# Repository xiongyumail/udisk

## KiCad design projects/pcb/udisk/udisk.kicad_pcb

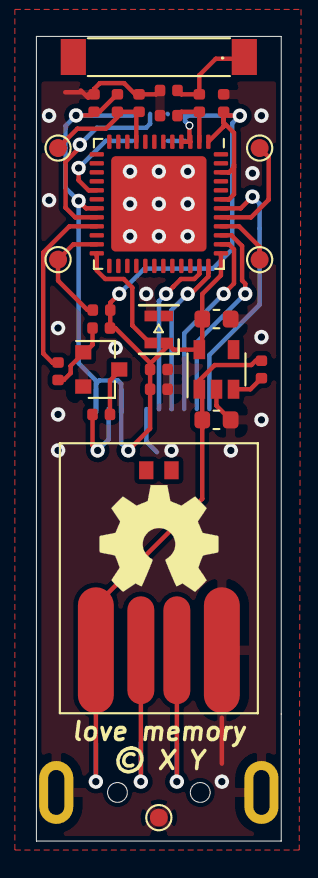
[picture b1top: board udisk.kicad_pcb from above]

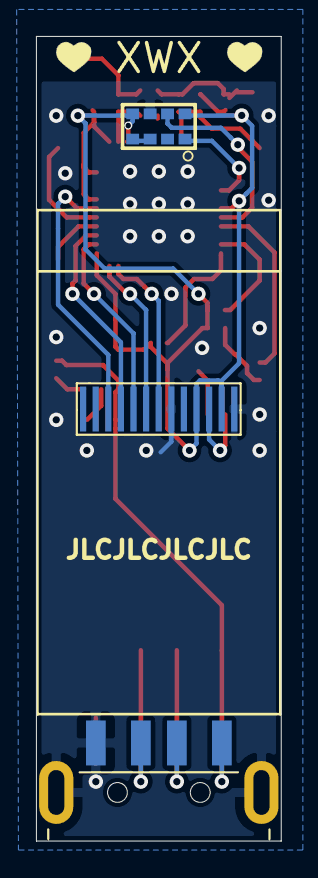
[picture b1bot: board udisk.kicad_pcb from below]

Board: 2 copper layers, 13.6 x 44.7 mm, 30 parts (3 on the bottom side), 25 nets.

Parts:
AE1: ANT; AN9520
C1, C2: 1uF; C_0603_1608Metric
C3, C4, C5, C8, C11: 0.1uF; C_0402_1005Metric
C6, C7: NC; C_0402_1005Metric
D1: WS2812B-0807
J1: USB_A; USB_A_2.0_Male
L1: NC; L_0402_1005Metric
LCD1: IPS0.9'160x80
Q1: S8050; SOT-23
R1: 100K; R_0402_1005Metric
R2: 1K; R_0402_1005Metric
R3, R5, R6: 10K; R_0402_1005Metric
R4: 10; R_0402_1005Metric
TP1: TXD; TestPoint_Pad_D1.0mm
TP2: RXD; TestPoint_Pad_D1.0mm
TP3: EN; TestPoint_Pad_D1.0mm
TP4: GPIO0; TestPoint_Pad_D1.0mm
TP5: GND; TestPoint_Pad_D1.0mm
U1: RT9013; SOT-23-5
U2: APDS-9960
U3: ESP32-PICO-D4; QFN-48-1EP_7x7mm_P0.5mm_EP5.3x5.3mm
U5: udisk

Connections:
+3V3: C2.1, C3.2, C4.1, C8.1, C11.1, D1.1, LCD1.10, LCD1.12, R3.1, R5.1, R6.1, U1.5, U2.5, U2.8, U3.1, U3.3, U3.4, U3.19, U3.37, U3.43, U3.46
/D+: J1.3, U5.3
/D-: J1.2, U5.2
/DIN: D1.4, U3.24
/ESP32-PICO-D4/EN: C5.1, R5.2, TP3.1, U3.9
/ESP32-PICO-D4/GPIO0: R6.2, TP4.1, U3.23
/ESP32-PICO-D4/RXD: TP2.1, U3.40
/ESP32-PICO-D4/TXD: TP1.1, U3.41
/LCD160x80/LEDK: LCD1.11, R4.1
/LCD_BLK: R2.2, U3.21
/LCD_CLK: LCD1.4, U3.39
/LCD_CS1: LCD1.7, U3.35
/LCD_DC: LCD1.5, U3.38
/LCD_MOSI: LCD1.3, U3.42
/LCD_RES: LCD1.6, U3.36
/SCL: U2.7, U3.20
/SDA: U2.1, U3.17
GND: C1.2, C2.2, C3.1, C4.2, C5.2, C6.2, C7.2, C8.2, C11.2, D1.3, J1.4, J1.5, LCD1.8, LCD1.13, Q1.2, TP5.1, U1.2, U2.6, U3.49, U5.4
unnamed: AE1.1, C6.1, L1.2
unnamed: C7.1, L1.1, U3.2
unnamed: Q1.1, R2.1, R3.2
unnamed: Q1.3, R4.2
unnamed: R1.1, U1.3
unnamed: U2.3, U2.4
VBUS: C1.1, J1.1, R1.2, U1.1, U5.1

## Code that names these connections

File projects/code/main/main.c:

#include <stdio.h>
#include <stdlib.h>
#include <stdio.h>
#include <time.h>
#include <sys/time.h>
#include <math.h>
#include "freertos/FreeRTOS.h"
#include "freertos/task.h"
#include "freertos/semphr.h"
#include "esp_log.h"
#include "lvgl.h"
#include "lcd.h"
#include "driver/gpio.h"
#include "esp_lua.h"
#include "gui.h"
#include "APDS9960.h"
#include "WS2812B.h"

static const char *TAG = "main";

#define LCD_CLK  22
#define LCD_MOSI 21
#define LCD_DC   19
#define LCD_RST  23
#define LCD_CS   18
#define LCD_BK   15

static lv_disp_t *disp[1];
// static lv_indev_t *indev[1];

static void IRAM_ATTR lv_disp_flush(lv_disp_drv_t * disp_drv, const lv_area_t * area, lv_color_t * color_p)
{
    uint32_t len = (sizeof(uint16_t) * ((area->y2 - area->y1 + 1)*(area->x2 - area->x1 + 1)));

    lcd_set_index(area->x1, area->y1, area->x2, area->y2);
    lcd_write_data((uint8_t *)color_p, len);

    lv_disp_flush_ready(disp_drv);
}

static void lv_tick_task(void * arg)
{
    while(1) {
        lv_tick_inc(10);
        vTaskDelay(10 / portTICK_RATE_MS);
    }
}

static void gui_task(void *arg)
{
    lcd_config_t lcd_config = {
        .clk_fre = 40 * 1000 * 1000,
        .pin_clk = LCD_CLK,
        .pin_mosi = LCD_MOSI,
        .pin_dc = LCD_DC,
        .pin_cs = LCD_CS,
        .pin_rst = LCD_RST,
        .pin_bk = LCD_BK,
        .max_buffer_size = 2 * 1024,
        .horizontal = 1 // 1: UP, 3： DOWN
    };

    lcd_init(&lcd_config);
    
    xTaskCreate(lv_tick_task, "lv_tick_task", 1024, NULL, 10, NULL);

    lv_init();

    /*Create an other buffer for double buffering*/
    static lv_disp_buf_t disp_buf;
    static lv_color_t *buf = NULL;
    buf = (lv_color_t *)heap_caps_malloc(sizeof(lv_color_t) * (160 * 80) / 4, MALLOC_CAP_DEFAULT);
    lv_disp_buf_init(&disp_buf, buf, NULL, (160 * 80) / 4);

    /*Create a display*/
    lv_disp_drv_t disp_drv;
    lv_disp_drv_init(&disp_drv);            /*Basic initialization*/
    disp_drv.buffer = &disp_buf;
    disp_drv.flush_cb = lv_disp_flush;    /*Used when `LV_VDB_SIZE != 0` in lv_conf.h (buffered drawing)*/
    disp_drv.hor_res = 160;
    disp_drv.ver_res = 80;
    disp[0] = lv_disp_drv_register(&disp_drv);

    lv_disp_set_default(disp[0]);

    gui_init(disp, NULL, lv_theme_material_init(0, NULL));

    while(1) {
        lv_task_handler();
        vTaskDelay(10 / portTICK_RATE_MS);
    }
}

#include "esp_lua_lib.h"

static int lcd_write(lua_State *L) 
{
    int ret = -1;
    char *io = luaL_checklstring(L, 1, NULL);

    ret = gui_write(io, luaL_checklstring(L, 2, NULL), 100 / portTICK_RATE_MS);

    if (ret == 0) {
        lua_pushboolean(L, true);
    } else {
        lua_pushboolean(L, false);
    }
    return 1;
}

static const luaL_Reg lcd_lib[] = {
    {"write", lcd_write},
    {NULL, NULL}
};

LUAMOD_API int esp_lib_lcd(lua_State *L) 
{
    xTaskCreate(gui_task, "gui_task", 4096, NULL, 5, NULL);

    luaL_newlib(L, lcd_lib);
    lua_pushstring(L, "0.1.0");
    lua_setfield(L, -2, "_version");
    return 1;
}

wsRGB_t rgb[1];

static int led_write(lua_State *L) 
{
    int ret = -1;

    rgb[0].r = luaL_checknumber(L, 1);
    rgb[0].g = luaL_checknumber(L, 2);
    rgb[0].b = luaL_checknumber(L, 3);
    WS2812B_setLeds(rgb, 1);
    lua_pushboolean(L, true);
    return 1;
}

static const luaL_Reg led_lib[] = {
    {"write", led_write},
    {NULL, NULL}
};

LUAMOD_API int esp_lib_led(lua_State *L) 
{
    WS2812B_init(RMT_CHANNEL_0, GPIO_NUM_4, 1);
    rgb[0].r = 0x00;
    rgb[0].g = 0x00;
    rgb[0].b = 0x00;
    WS2812B_setLeds(rgb, 1);

    luaL_newlib(L, led_lib);
    lua_pushstring(L, "0.1.0");
    lua_setfield(L, -2, "_version");
    return 1;
}

#include "driver/i2c.h"
#include "esp_system.h"

#define APDS9960_I2C_MASTER_SCL_IO           (gpio_num_t)13          /*!< gpio number for I2C master clock */
#define APDS9960_I2C_MASTER_SDA_IO           (gpio_num_t)14          /*!< gpio number for I2C master data  */
#define APDS9960_I2C_MASTER_NUM              I2C_NUM_1   /*!< I2C port number for master dev */
#define APDS9960_I2C_MASTER_TX_BUF_DISABLE   0           /*!< I2C master do not need buffer */
#define APDS9960_I2C_MASTER_RX_BUF_DISABLE   0           /*!< I2C master do not need buffer */
#define APDS9960_I2C_MASTER_FREQ_HZ          100000      /*!< I2C master clock frequency */

apds9960_handle_t apds9960 = NULL;

/**
 * @brief i2c master initialization
 */
static void i2c_sensor_apds9960_init()
{
    int i2c_master_port = APDS9960_I2C_MASTER_NUM;
    i2c_config_t conf;
    conf.mode = I2C_MODE_MASTER;
    conf.sda_io_num = APDS9960_I2C_MASTER_SDA_IO;
    conf.sda_pullup_en = GPIO_PULLUP_ENABLE;
    conf.scl_io_num = APDS9960_I2C_MASTER_SCL_IO;
    conf.scl_pullup_en = GPIO_PULLUP_ENABLE;
    conf.master.clk_speed = APDS9960_I2C_MASTER_FREQ_HZ;
    i2c_param_config(i2c_master_port, &conf);
    i2c_driver_install(i2c_master_port, conf.mode, APDS9960_I2C_MASTER_TX_BUF_DISABLE, APDS9960_I2C_MASTER_RX_BUF_DISABLE, 0);

    apds9960 = apds9960_create(i2c_master_port, APDS9960_I2C_ADDRESS);
}

static int apds_read(lua_State *L) 
{
    int ret = -1;
    char *io = luaL_checklstring(L, 1, NULL);

    if (strcmp(io, "distance") == 0) {
        lua_pushinteger(L, apds9960_read_proximity(apds9960));
    } else {
        lua_pushboolean(L, false);
    }

    return 1;
}

static const luaL_Reg apds_lib[] = {
    {"read", apds_read},
    {NULL, NULL}
};

LUAMOD_API int esp_lib_apds(lua_State *L) 
{
    i2c_sensor_apds9960_init();
    apds9960_gesture_init(apds9960);
    apds9960_set_proximity_gain(apds9960, APDS9960_PGAIN_8X);

    luaL_newlib(L, apds_lib);
    lua_pushstring(L, "0.1.0");
    lua_setfield(L, -2, "_version");
    return 1;
}

static const luaL_Reg mylibs[] = {
    {"sys", esp_lib_sys},
    {"net", esp_lib_net},
    {"web", esp_lib_web},
    {"mqtt", esp_lib_mqtt},
    {"httpd", esp_lib_httpd},
    {"ramf", esp_lib_ramf},
    {"lcd", esp_lib_lcd},
    {"led", esp_lib_led},
    {"apds", esp_lib_apds},
    {NULL, NULL}
};

const char LUA_SCRIPT_INIT[] = " \
assert(sys.init()) \
dofile(\'/lua/init.lua\') \
";

void lua_task(void *arg)
{
    char *ESP_LUA_ARGV[5] = {"./lua", "-i", "-e", LUA_SCRIPT_INIT, NULL}; // enter interactive mode after executing 'script'

    esp_lua_init(NULL, NULL, mylibs);

    while (1) {
        esp_lua_main(4, ESP_LUA_ARGV);
        printf("lua exit\n");
        vTaskDelay(2000 / portTICK_RATE_MS);
    }

    vTaskDelete(NULL);
}

void app_main()
{
    esp_log_level_set("*", ESP_LOG_ERROR);
    xTaskCreate(lua_task, "lua_task", 10240, NULL, 5, NULL);
}

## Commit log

2020-05-26 feature(udisk): add pcb
2020-05-31 feature(pcb): pcb ok
2020-05-31 feature(pcb): update kicad-lib
2020-05-31 fix upcb issue
2020-06-07 udisk ok
2020-06-09 udisk images test ok
2020-06-10 udisk img test ok
2020-06-10 test gui
2020-06-10 self-hosted test
2020-06-11 add OUTPUT_PATH
2020-06-11 test
2020-06-11 Create main.yml (#5)
    * self-hosted test
    * add OUTPUT_PATH
2020-06-11 test deploy
2020-06-11 Feature/ci (#6)
    * test deploy
2020-06-11 test ci
2020-06-11 test ci (#7)
2020-06-11 test ci if
2020-06-11 test ci if (#8)
2020-06-11 test esp-idf
2020-06-11 test espressif
2020-06-11 test code build
2020-06-11 test code buildls
2020-06-11 test self-hosted build
2020-06-11 test flash
2020-06-11 feature(ci): esp32 ci test
2020-06-11 update checkout and cache
2020-06-11 update checkout and cache to master
2020-06-11 feature(ci): esp32 ci test (#9)
    * feature(ci): esp32 ci test
    * update checkout and cache to master
2020-06-12 feature(ci): add artifact
2020-06-12 test artifact
2020-06-12 feature(ci): add artifact (#10)
    * feature(ci): add artifact
2020-06-12 test download-artifact
2020-06-12 add runs-on
2020-06-12 fix path
2020-06-12 Feature/test down artifact (#11)
    * test download-artifact
2020-06-12 scp add -r
2020-06-19 add esp-idf and gen md5
    update ci and lua
2020-06-23 add ws2812
2020-06-29 lua update
2020-06-29 Feature/ws2812 (#12)
    * add ws2812
    * lua update
2020-06-30 update lua and ci
2020-06-30 upload main.lua
2020-06-30 add version
2020-06-30 add led write
2020-06-30 update httpd
2020-06-30 fix lua path
2020-06-30 add mqtt
2020-06-30 test lcd
2020-08-07 add udisk 3d
2020-08-13 add apds9960 to lua
2020-08-13 test proximity
2020-08-13 test apds9960
2020-08-13 test offline
2020-08-13 default do not connect wifi
2020-08-13 add delay

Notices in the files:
projects/pcb/udisk/udisk.kicad_pcb:
© X Y
